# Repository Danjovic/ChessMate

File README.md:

# ChessMate

The ChessMate is an AVR ATmega328P running at 25 MHz with chess Engine based on recursive negamax search micro-Max 4.8 by [H.G. Muller]
The hash table was removed by [Andre Adrian].

Our contribution are the following features:
- Included [Threefold repetition rule] using Compact Chess Representation of history boards ([C.C.R.]), we made it valid 
for the last 15 boards with 32 bytes per board; so the history boards occupies 480 bytes of RAM.
- Included the [Fifty-move rule] check from [fairy-Max].

Processing Speed:
For instance, the 32-bit test version of Rybka on AMD 64-bit CPU running on 2.4Ghz achieves 104 Knps (thousands of nodes 
per second); refer to [C.C.R.].

The ATmega328P ChessMate at 25 MHz approach, can reach ~1.3 Knps (1298.1 nodes/s).

A node refers to a branch of play the computer investigated. 

[H.G. Muller]: <http://home.hccnet.nl/h.g.muller/max-src2.html>
[Andre Adrian]: <http://www.andreadrian.de/schach/#Selbstbau_Schachcomputer_SHAH>
[C.C.R.]: <http://www.doiserbia.nb.rs/img/doi/0354-0243/2012/0354-02431200011V.pdf>
[fairy-Max]: <http://home.hccnet.nl/h.g.muller/CVfairy.html>
[Demo Video]: <https://youtu.be/5uhqcVmfm20>
[Hackaday Entry]: <https://hackaday.io/project/8705-chess-mate>
[Threefold repetition rule]: <https://en.wikipedia.org/wiki/Threefold_repetition>
[Fifty-move rule]: <https://en.wikipedia.org/wiki/Fifty-move_rule>

> First release at 15-Feb-2016

How to play:
Initially, it should appear "PLAY" at the display
- Press and hold "NEW" + the number of level
- Enter your 4 digit move then press "ENTER"
- Wait for lily thinking (it will be displayed blinking dots)
- The lily move will be displayed just after the thinking
- If you entered an erroneous digit; press "CLR", short press, to delete one digit
- If you want to delete all digits entered, press and hold "CLR"

See the [Demo Video] and the [Hackaday Entry]

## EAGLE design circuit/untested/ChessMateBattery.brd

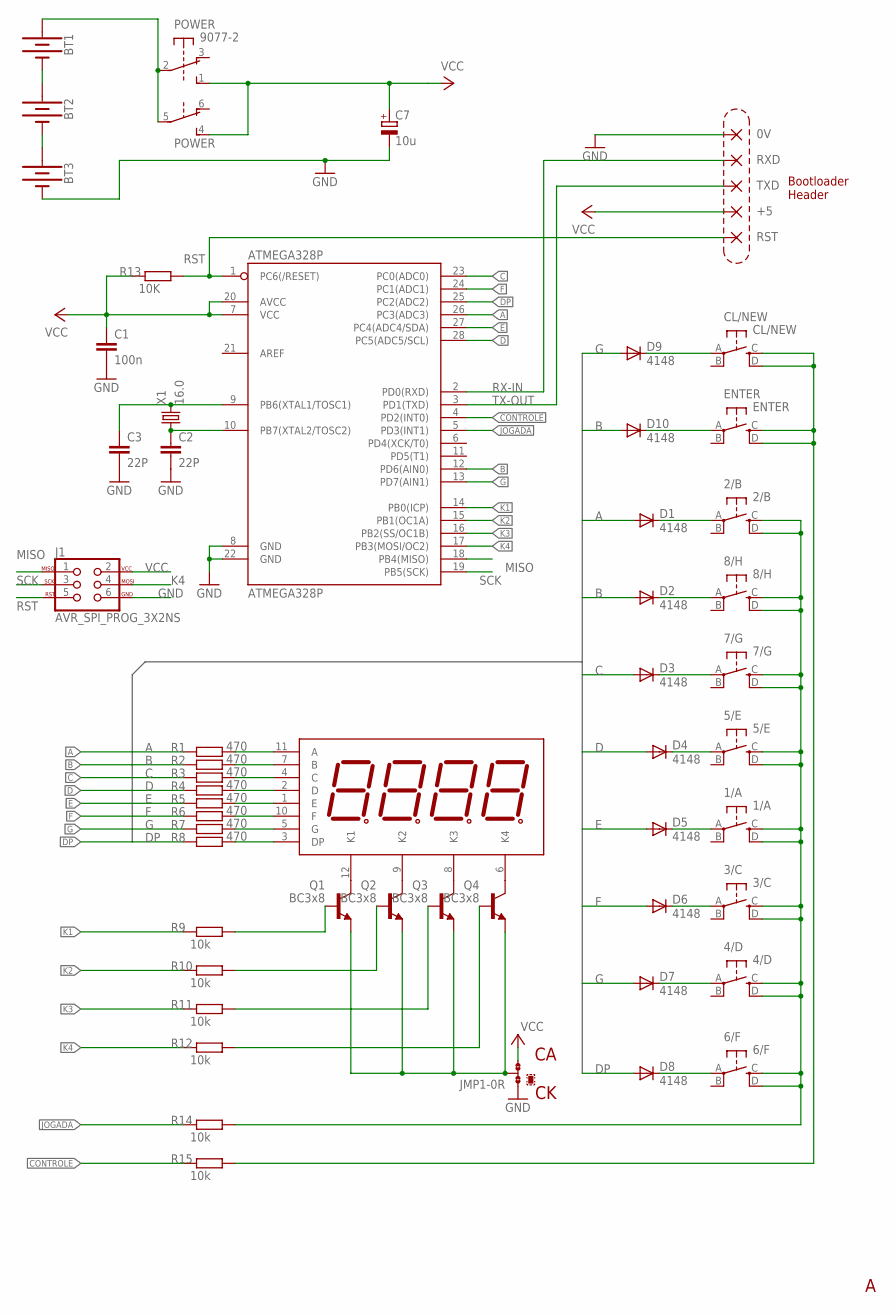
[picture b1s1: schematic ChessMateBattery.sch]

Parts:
0V: 2,15/1,0
1/A: 1/A; TACT_SW
2/B: 2/B; TACT_SW
3/C: 3/C; TACT_SW
4/D: 4/D; TACT_SW
5/E: 5/E; TACT_SW
6/F: 6/F; TACT_SW
7/G: 7/G; TACT_SW
8/H: 8/H; TACT_SW
+5: 2,15/1,0
ATMEGA328P: ATMEGA328P; DIL28-3
BT1, BT2, BT3: BATTERY-AAA_KIT; BATTERY-AAA-KIT
C1: 100n; C050-024X044L
C2, C3: 22P; C025-024X044L
C7: 10u; TT2D7L
CL/NEW: CL/NEW; TACT_SW
D1, D2, D3, D4, D5, D6, D7, D8, D9, D10: 4148; DO35-7
DISPLAY: 4_DIGIT-TOF3461BH-N; TOF3461BH-N
ENTER: ENTER; TACT_SW
J1: AVR_SPI_PROG_3X2NS; 2X3-NS
JMP1: 0R-JUMPA; A0R-JMP
POWER: 9077-2
Q1, Q2, Q3, Q4: BC3x8; TO92-EBC
R1, R2, R3, R4, R5, R6, R7, R8: 470; 0204/7L
R9, R10, R11, R12, R14, R15: 10k; 0204/7L
R13: 10K; 0204/5L
RST: 2,15/1,0
RXD: 2,15/1,0
TXD: 2,15/1,0
X1: 16.0; HC49/SL

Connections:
A: ATMEGA328P.26 (PC3(ADC3)), D1.A, R1.1
B: ATMEGA328P.12 (PD6(AIN0)), D2.A, D10.A, R2.1
C: ATMEGA328P.23 (PC0(ADC0)), D3.A, R3.1
CONTROLE: ATMEGA328P.4 (PD2(INT0)), R15.1
CONTROLE_: CL/NEW.C (S), CL/NEW.D (S1), ENTER.C (S), ENTER.D (S1), R15.2
D: ATMEGA328P.28 (PC5(ADC5/SCL)), D4.A, R4.1
DP: ATMEGA328P.25 (PC2(ADC2)), D8.A, R8.1
E: ATMEGA328P.27 (PC4(ADC4/SDA)), D5.A, R5.1
F: ATMEGA328P.24 (PC1(ADC1)), D6.A, R6.1
G: ATMEGA328P.13 (PD7(AIN1)), D7.A, D9.A, R7.1
GND: 0V.1, ATMEGA328P.8 (GND), ATMEGA328P.22 (GND), BT3.GND@1 (-), C1.2, C2.2, C3.2, C7.-, J1.6, JMP1.1
JOGADA: ATMEGA328P.5 (PD3(INT1)), R14.1
JOGADA_C: 1/A.C (S), 1/A.D (S1), 2/B.C (S), 2/B.D (S1), 3/C.C (S), 3/C.D (S1), 4/D.C (S), 4/D.D (S1), 5/E.C (S), 5/E.D (S1), 6/F.C (S), 6/F.D (S1), 7/G.C (S), 7/G.D (S1), 8/H.C (S), 8/H.D (S1), R14.2
K1: ATMEGA328P.14 (PB0(ICP)), R9.1
K2: ATMEGA328P.15 (PB1(OC1A)), R10.1
K3: ATMEGA328P.16 (PB2(SS/OC1B)), R11.1
K4: ATMEGA328P.17 (PB3(MOSI/OC2)), J1.4, R12.1
MISO: ATMEGA328P.18 (PB4(MISO)), J1.1
unnamed: DISPLAY.11 (A), R1.2
unnamed: DISPLAY.7 (B), R2.2
unnamed: DISPLAY.4 (C), R3.2
unnamed: DISPLAY.2 (D), R4.2
unnamed: DISPLAY.1 (E), R5.2
unnamed: DISPLAY.10 (F), R6.2
unnamed: DISPLAY.5 (G), R7.2
unnamed: DISPLAY.3 (DP), R8.2
unnamed: Q1.B, R9.2
unnamed: Q2.B, R10.2
unnamed: Q3.B, R11.2
unnamed: Q4.B, R12.2
unnamed: DISPLAY.12 (K1), Q1.C
unnamed: DISPLAY.9 (K2), Q2.C
unnamed: DISPLAY.8 (K3), Q3.C
unnamed: DISPLAY.6 (K4), Q4.C
unnamed: ATMEGA328P.9 (PB6(XTAL1/TOSC1)), C3.1, X1.2
unnamed: ATMEGA328P.10 (PB7(XTAL2/TOSC2)), C2.1, X1.1
unnamed: BT1.PWR@1 (+), POWER.2, POWER.5
unnamed: CL/NEW.A, D9.C
unnamed: D10.C, ENTER.A
unnamed: 2/B.A, D1.C
unnamed: 8/H.A, D2.C
unnamed: 5/E.A, D4.C
unnamed: 1/A.A, D5.C
unnamed: 3/C.A, D6.C
unnamed: 4/D.A, D7.C
unnamed: 6/F.A, D8.C
unnamed: 7/G.A, D3.C
unnamed: BT1.GND@1 (-), BT2.PWR@1 (+)
unnamed: BT2.GND@1 (-), BT3.PWR@1 (+)
unnamed: JMP1.2, Q1.E, Q2.E, Q3.E, Q4.E
RST: ATMEGA328P.1 (PC6(/RESET)), J1.5, R13.2, RST.1
RX-IN: ATMEGA328P.2 (PD0(RXD)), RXD.1
SCK: ATMEGA328P.19 (PB5(SCK)), J1.3
TX-OUT: ATMEGA328P.3 (PD1(TXD)), TXD.1
VCC: +5.1, ATMEGA328P.7 (VCC), ATMEGA328P.20 (AVCC), C1.1, C7.+, J1.2, JMP1.3, POWER.1 (S), POWER.4 (S), R13.1

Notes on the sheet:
Bootloader Header

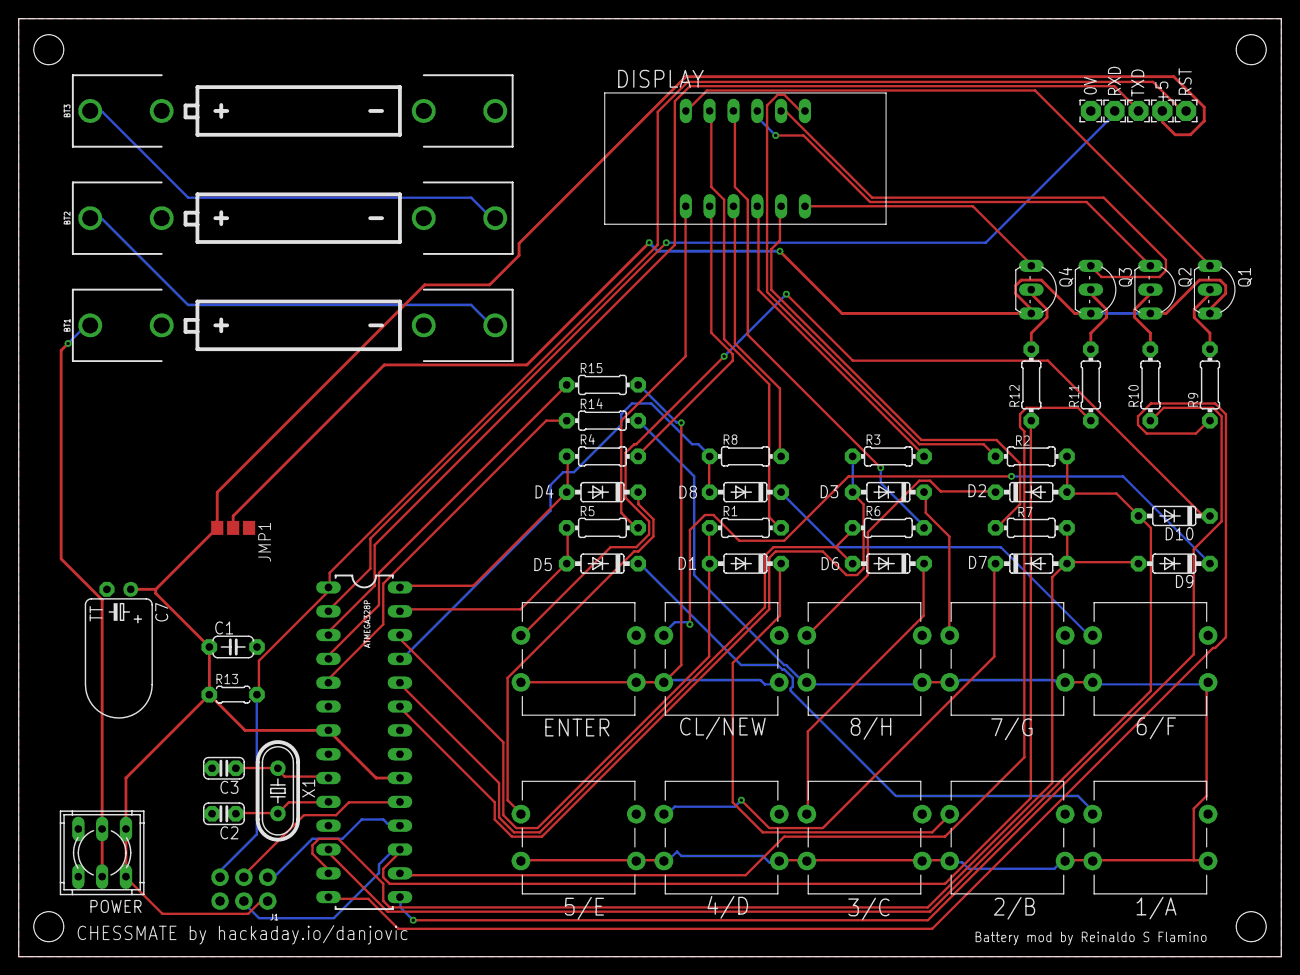
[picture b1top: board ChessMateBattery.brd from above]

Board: 2 copper layers, 134.6 x 100.0 mm, 57 parts (0 on the bottom side), 55 nets.

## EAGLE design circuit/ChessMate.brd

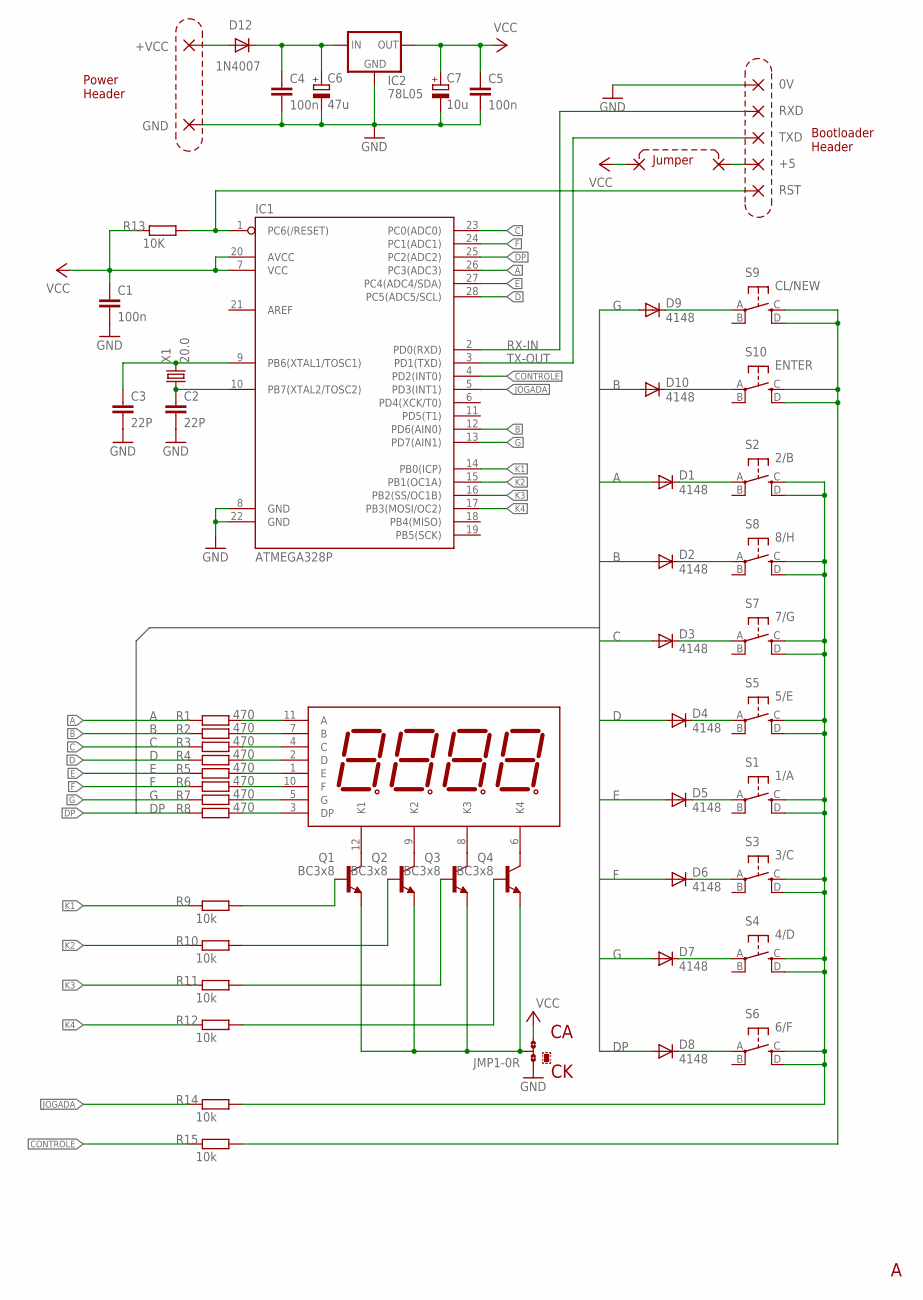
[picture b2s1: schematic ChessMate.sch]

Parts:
0V: 2,15/1,0
+5: 2,15/1,0
+VCC: 2,15/1,0
C1, C4, C5: 100n; C050-024X044L
C2, C3: 22P; C025-024X044L
C6: 47u; TT2D7L
C7: 10u; TT2D7L
D1, D2, D3, D4, D5, D6, D7, D8, D9, D10: 4148; DO35-7
D12: 1N4007; DO41-7.6L
GND: 2,15/1,0
IC1: ATMEGA328P; DIL28-3
IC2: 78L05; TO92_
JMP1: 0R-JUMPA; A0R-JMP
LD1: 4_DIGIT-TOF3461BH-N; TOF3461BH-N
PAD1, PAD2: 1,6/0,8
Q1, Q2, Q3, Q4: BC3x8; TO92-EBC
R1, R2, R3, R4, R5, R6, R7, R8: 470; 0204/7L
R9, R10, R11, R12, R14, R15: 10k; 0204/7L
R13: 10K; 0204/5L
RST: 2,15/1,0
RXD: 2,15/1,0
S1: 1/A; TACT_SW
S2: 2/B; TACT_SW
S3: 3/C; TACT_SW
S4: 4/D; TACT_SW
S5: 5/E; TACT_SW
S6: 6/F; TACT_SW
S7: 7/G; TACT_SW
S8: 8/H; TACT_SW
S9: CL/NEW; TACT_SW
S10: ENTER; TACT_SW
TXD: 2,15/1,0
X1: 20.0; HC49/SL

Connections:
A: D1.A, IC1.26 (PC3(ADC3)), R1.1
B: D2.A, D10.A, IC1.12 (PD6(AIN0)), R2.1
C: D3.A, IC1.23 (PC0(ADC0)), R3.1
CONTROLE: IC1.4 (PD2(INT0)), R15.1
CONTROLE_: R15.2, S9.C (S), S9.D (S1), S10.C (S), S10.D (S1)
D: D4.A, IC1.28 (PC5(ADC5/SCL)), R4.1
DP: D8.A, IC1.25 (PC2(ADC2)), R8.1
E: D5.A, IC1.27 (PC4(ADC4/SDA)), R5.1
F: D6.A, IC1.24 (PC1(ADC1)), R6.1
G: D7.A, D9.A, IC1.13 (PD7(AIN1)), R7.1
GND: 0V.1, C1.2, C2.2, C3.2, C4.2, C5.2, C6.-, C7.-, GND.1, IC1.8 (GND), IC1.22 (GND), IC2.2 (GND), JMP1.1
JOGADA: IC1.5 (PD3(INT1)), R14.1
JOGADA_C: R14.2, S1.C (S), S1.D (S1), S2.C (S), S2.D (S1), S3.C (S), S3.D (S1), S4.C (S), S4.D (S1), S5.C (S), S5.D (S1), S6.C (S), S6.D (S1), S7.C (S), S7.D (S1), S8.C (S), S8.D (S1)
K1: IC1.14 (PB0(ICP)), R9.1
K2: IC1.15 (PB1(OC1A)), R10.1
K3: IC1.16 (PB2(SS/OC1B)), R11.1
K4: IC1.17 (PB3(MOSI/OC2)), R12.1
unnamed: LD1.11 (A), R1.2
unnamed: LD1.7 (B), R2.2
unnamed: LD1.4 (C), R3.2
unnamed: LD1.2 (D), R4.2
unnamed: LD1.1 (E), R5.2
unnamed: LD1.10 (F), R6.2
unnamed: LD1.5 (G), R7.2
unnamed: LD1.3 (DP), R8.2
unnamed: Q1.B, R9.2
unnamed: Q2.B, R10.2
unnamed: Q3.B, R11.2
unnamed: Q4.B, R12.2
unnamed: LD1.12 (K1), Q1.C
unnamed: LD1.9 (K2), Q2.C
unnamed: LD1.8 (K3), Q3.C
unnamed: LD1.6 (K4), Q4.C
unnamed: IC1.1 (PC6(/RESET)), R13.2, RST.1
unnamed: C3.1, IC1.9 (PB6(XTAL1/TOSC1)), X1.2
unnamed: C2.1, IC1.10 (PB7(XTAL2/TOSC2)), X1.1
unnamed: +VCC.1, D12.A
unnamed: D9.C, S9.A
unnamed: D10.C, S10.A
unnamed: D1.C, S2.A
unnamed: D2.C, S8.A
unnamed: D4.C, S5.A
unnamed: D5.C, S1.A
unnamed: D6.C, S3.A
unnamed: D7.C, S4.A
unnamed: D8.C, S6.A
unnamed: D3.C, S7.A
unnamed: +5.1, PAD2.1
unnamed: C4.1, C6.+, D12.C, IC2.3 (IN)
unnamed: JMP1.2, Q1.E, Q2.E, Q3.E, Q4.E
RX-IN: IC1.2 (PD0(RXD)), RXD.1
TX-OUT: IC1.3 (PD1(TXD)), TXD.1
VCC: C1.1, C5.1, C7.+, IC1.7 (VCC), IC1.20 (AVCC), IC2.1 (OUT), JMP1.3, PAD1.1, R13.1

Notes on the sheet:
Bootloader Header
Power Header
Jumper

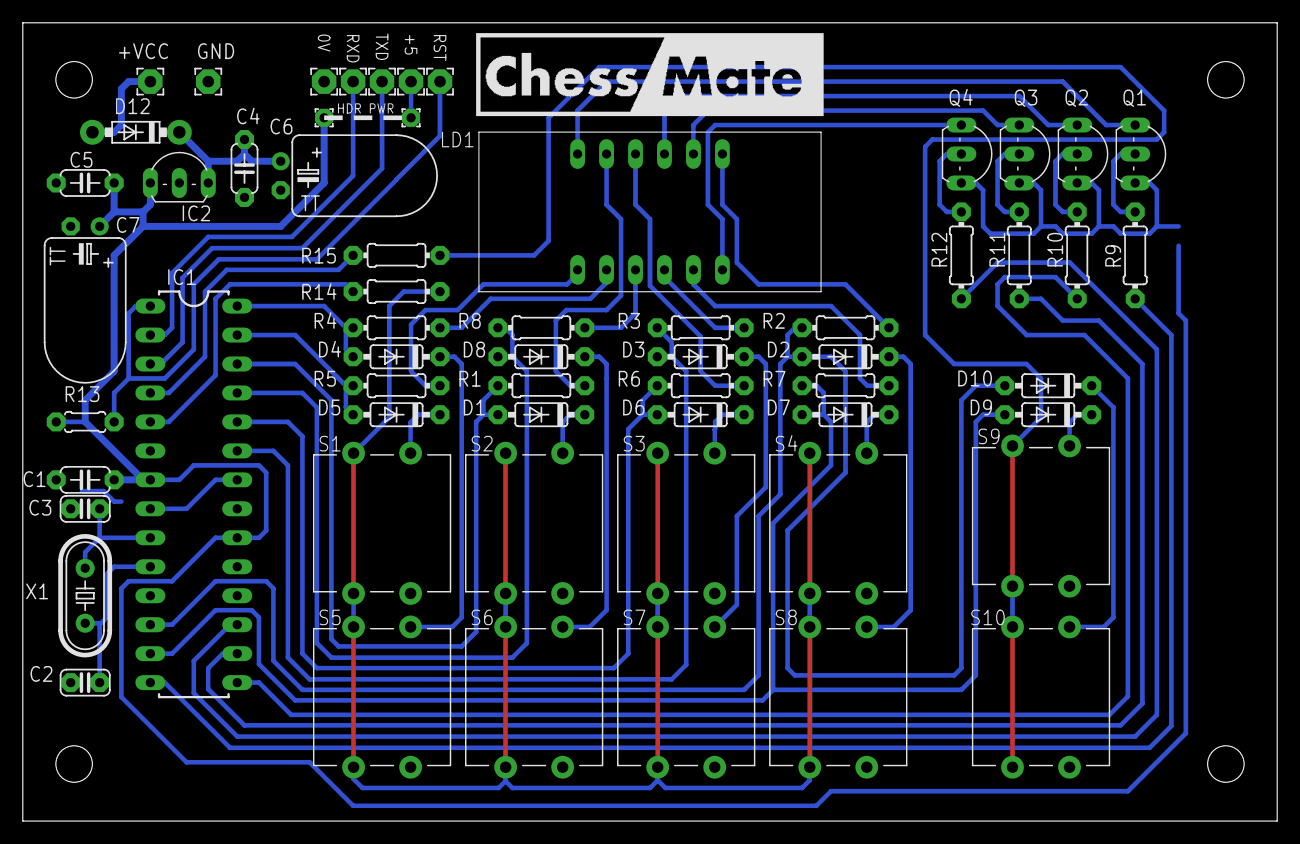
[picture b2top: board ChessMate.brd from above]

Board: 2 copper layers, 110.0 x 70.0 mm, 62 parts (1 on the bottom side), 53 nets.

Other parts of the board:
U$1: PB108_SMALL_HOLES

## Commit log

2015-12-05 :boom::camel: Added .gitattributes & .gitignore files
2015-12-08 added eagle temp files to gitignore
2015-12-08 First code
2015-12-15 Debounce routines ready
2016-02-15 Rename Makefile to Makefile.bak
2016-02-15 Rename main.c to main.bak
2016-02-15 Create Makefile
2016-02-15 Update Makefile
2018-08-28 Add files via upload
    battery mod
2018-09-19 chessmate battery mod not working - moved to diff directory

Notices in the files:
parts and their libraries:
SparkFun-DigitalIC: Licensing: Creative Commons ShareAlike 4.0 International - https://creativecommons.org/licenses/by-sa/4.0
